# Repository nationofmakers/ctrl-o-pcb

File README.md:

# ctrl-o-pcb
Circuit Boards for Ctrl-O

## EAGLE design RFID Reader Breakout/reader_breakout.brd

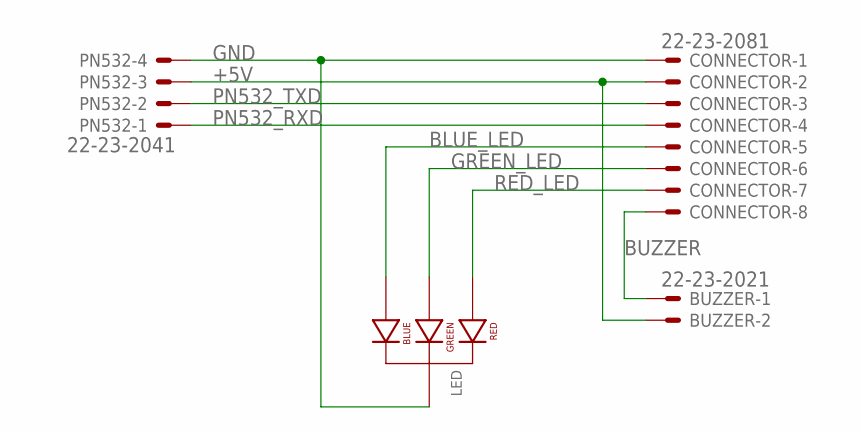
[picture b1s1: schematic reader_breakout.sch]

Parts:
BUZZER: 22-23-2021
CONNECTOR: 22-23-2081
LED: LED-RGB-CC-THRUCLEAR; LED-RGB-THRU
PN532: 22-23-2041

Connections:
+5V: BUZZER.2, CONNECTOR.2, PN532.3
BLUE_LED: CONNECTOR.5, LED.4 (BLUE_CATHODE)
BUZZER: BUZZER.1, CONNECTOR.8
GND: CONNECTOR.1, LED.2 (CATHODE), PN532.4
GREEN_LED: CONNECTOR.6, LED.3 (GREEN_CATHODE)
PN532_RXD: CONNECTOR.4, PN532.1
PN532_TXD: CONNECTOR.3, PN532.2
RED_LED: CONNECTOR.7, LED.1 (RED_CATHODE)

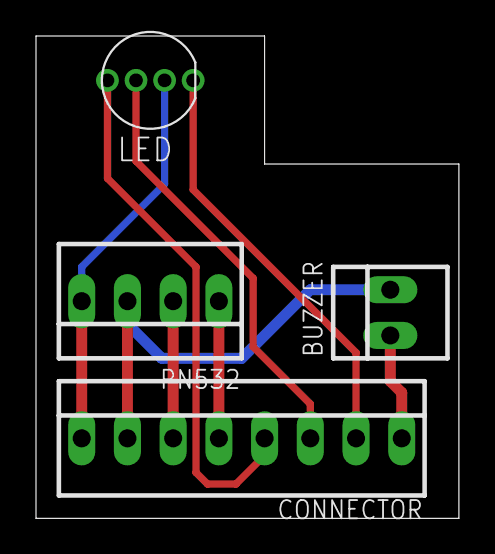
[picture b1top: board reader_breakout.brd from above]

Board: 2 copper layers, 23.5 x 26.8 mm, 4 parts (0 on the bottom side), 8 nets.

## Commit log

2016-08-05 Adding first version of board.
2016-08-05 Adding wiring chart for new board
2016-08-06 Fix to formatting

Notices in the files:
parts and their libraries:
SparkFun-LED: Licensing: Creative Commons ShareAlike 4.0 International - https://creativecommons.org/licenses/by-sa/4.0
